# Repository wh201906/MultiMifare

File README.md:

# MultiMifare

A single pcb contains two Mifare chips  
PCB Antenna created from https://kbeckmann.github.io/nfc-antenna-generator/  
This is a KiCad project.

## Preview

## Notice
I made the schematic symbol and the PCB footprint of the Mifare chip with manual measurement rather than a given size. So I'm not sure if they are reliable. The PCB itself works fine, though.

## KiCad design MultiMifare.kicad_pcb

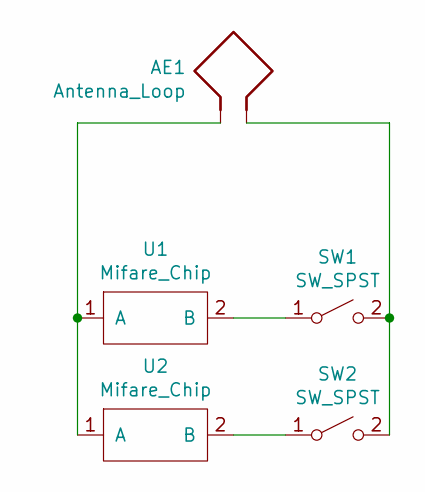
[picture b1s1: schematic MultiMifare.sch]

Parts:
AE1: Antenna_Loop; ant_50_60_2400
SW1, SW2: SW_SPST; SW_SPST_TL3342
U1, U2: Mifare_Chip

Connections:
unnamed: AE1.1, SW1.2 (B), SW2.2 (B)
unnamed: AE1.2, U1.1 (A), U2.1 (A)
unnamed: SW1.1 (A), U1.2 (B)
unnamed: SW2.1 (A), U2.2 (B)

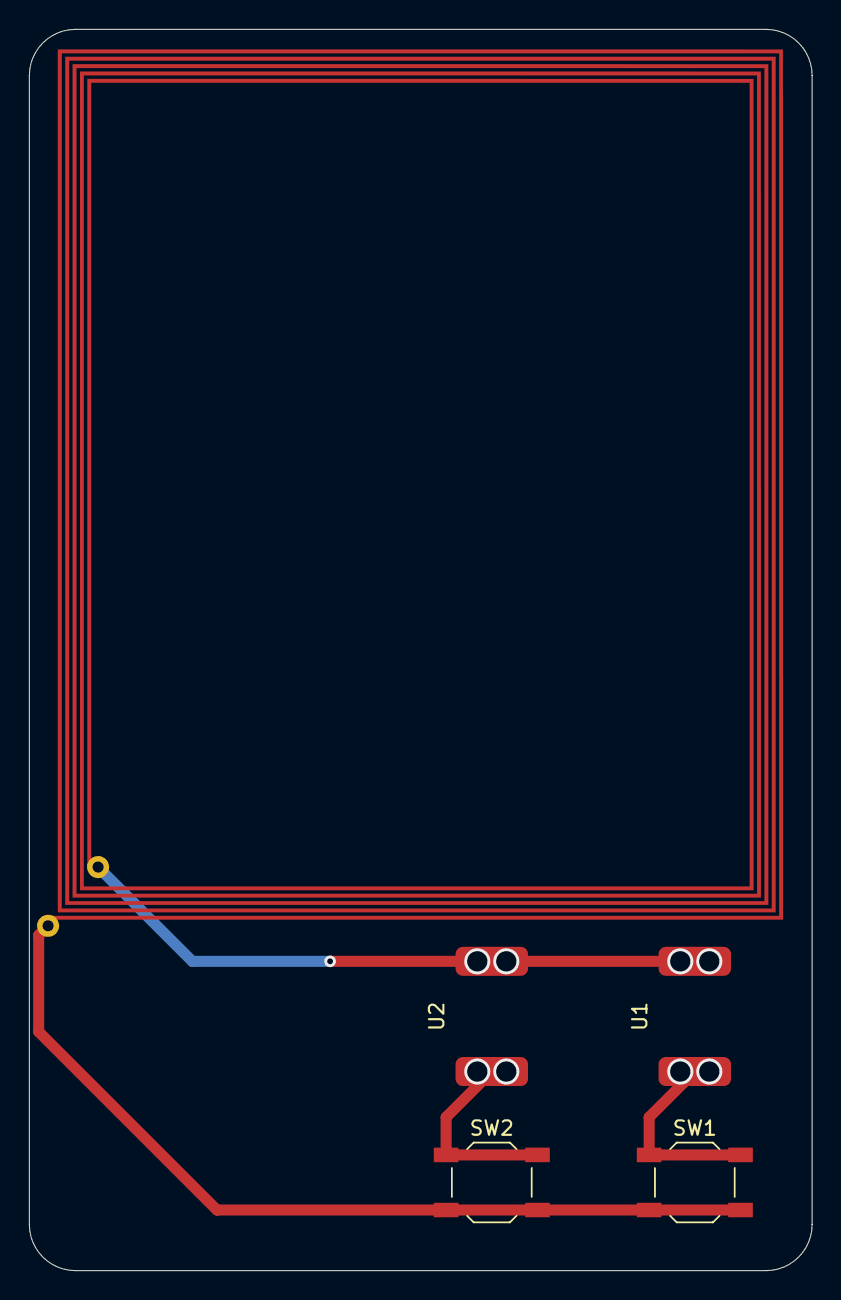
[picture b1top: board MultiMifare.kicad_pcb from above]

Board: 2 copper layers, 54.0 x 85.6 mm, 5 parts (0 on the bottom side), 4 nets.

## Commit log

2021-05-10 MultiMifare: First commit
    Add Edge cut(53.98mm*85.6mm, r=3.18mm)
2021-05-10 Misc
2021-05-10 My first ugly KiCad project
2021-05-10 DRC passed
2021-05-10 gerber output
2021-05-17 Easier to solder
2021-05-17 New antenna
    50*60mm, 1mm width, 1mm space, 5 turn
2021-06-09 Add README.md
2021-06-09 Create LICENSE
2021-06-09 Modify README.md
